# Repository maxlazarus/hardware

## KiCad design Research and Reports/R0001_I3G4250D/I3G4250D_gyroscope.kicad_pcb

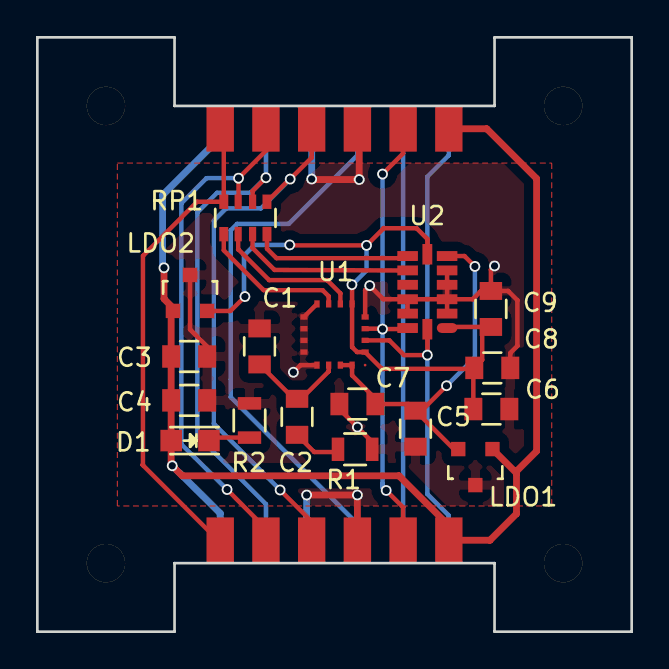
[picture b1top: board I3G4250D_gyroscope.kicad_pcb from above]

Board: 2 copper layers, 33.0 x 33.0 mm, 19 parts (0 on the bottom side), 19 nets.

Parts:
C1: 10nF; C_0805
C2: 0.47uF; C_0805
C3, C4, C5, C6: 1uF; C_0805
C7: 10uF tantalum; C_0805
C8, C9: 0.1uF; C_0805
D1: POW; LED-0805
J1: modular8_rev3_comms_in; modular8_rev3_edge
J2: modular8_rev3_comms_out; modular8_rev3_edge
LDO1, LDO2: AP7313-33SAG-7; SOT-23
R1: 10k; R_0805
R2: 680; R_0805
RP1: R_PACK4; R_Array_Convex_4x0603
U1: I3G4250DTR; LGA-16
U2: ADXL343; LGACC-14-1

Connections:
+3.3VP: C5.1, C7.1, LDO1.2, U1.15, U1.16, U2.6
+3V3: C6.1, C8.1, C9.1, LDO2.2, U1.1, U1.5, U2.1, U2.7
+5V: C3.1, C4.1, D1.2, J1.2, J1.11, J2.1, J2.12, LDO1.1, LDO2.1
/SCL: J1.12, J2.2, U1.2, U2.14
/SDA: J1.9, J2.3, U1.3, U2.13
/THRU1: J1.1, J2.11, RP1.4
/THRU2: J1.3, J2.9, RP1.3
/THRU3: J1.5, J2.7, RP1.1
/THRU4: J1.10, J2.4
/THRU5: J1.8, J2.6
/THRU6: J1.4, J2.10, RP1.2
/U1_INT1: RP1.5, U1.7
/U1_INT2: RP1.6, U1.6
/U2_INT1: RP1.8, U2.8
/U2_INT2: RP1.7, U2.9
GND: C1.2, C3.2, C4.2, C5.2, C6.2, C7.2, C8.2, C9.2, J1.6, J1.7, J2.5, J2.8, LDO1.3, LDO2.3, R1.2, R2.2, U1.4, U1.8, U1.9, U1.10, U1.11, U1.12, U1.13, U2.2, U2.3, U2.4, U2.5, U2.11, U2.12
unnamed: C1.1, C2.1, U1.14
unnamed: C2.2, R1.1
unnamed: D1.1, R2.1

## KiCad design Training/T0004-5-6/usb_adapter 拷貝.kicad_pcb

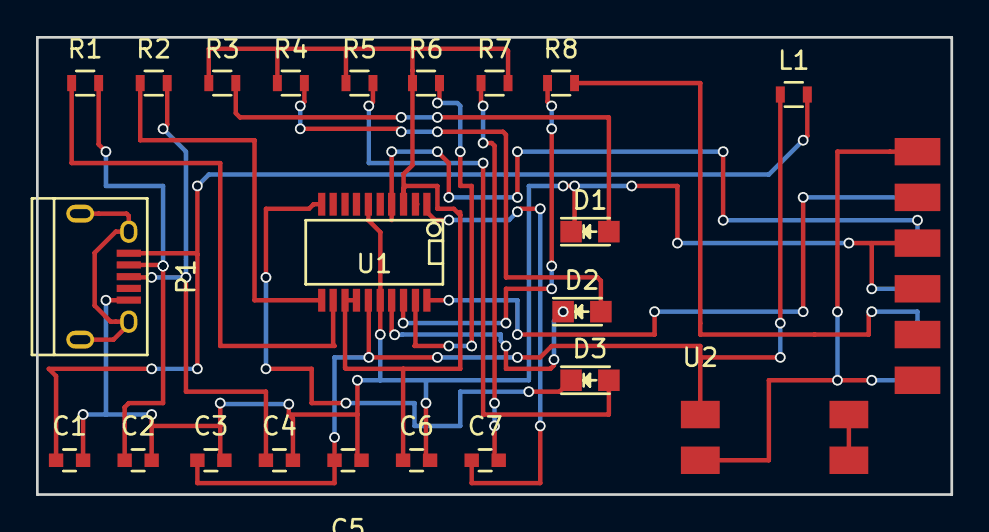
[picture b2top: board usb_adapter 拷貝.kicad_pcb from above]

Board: 2 copper layers, 50.8 x 25.4 mm, 23 parts (0 on the bottom side), 21 nets.

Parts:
C1: 10nF; C_0603
C2, C4: 47pF; C_0603
C3: 4.7uF; C_0603
C5, C6, C7: 0.1uF; C_0603
D1: POW; LED-0805
D2: RX; LED-0805
D3: TX; LED-0805
J1: modular8_rev3_comms_out; modular8_rev3_edge
L1: FERRITE BEAD; R_0603
P1: USB_OTG; USB_Micro-B
R1, R2: 27; R_0603
R3, R4, R5: 680; R_0603
R6, R7, R8: 10k; R_0603
U1: FT231X; SSOP-20
U2: TE_1825058-1; DIPSWITCH_SMT_ALCO_2CCT

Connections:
+3V3: C6.1, R3.1, R4.1, R5.1, R6.1, R7.2, U1.3, U1.13, U1.14
+5V: C3.1, C5.1, L1.1, U1.15, U2.1
/POWER_OUT: J1.1, J1.12, U2.2
/PROGRAM: C7.2, R7.1
/RX: J1.6, U1.4
/TX: J1.4, U1.20
/TXDEN: R8.1, U1.18
/~RXLED: D2.1, U1.17
/~SLEEP: R6.2, U1.19
/~TXLED: D3.1, U1.10
GND: C1.2, C2.2, C3.2, C4.2, C5.2, C6.2, D1.1, J1.5, J1.8, P1.5, U1.6, U1.16
unnamed: C1.1, L1.2, P1.1
unnamed: C2.1, P1.2, R1.2
unnamed: C4.1, P1.3, R2.2
unnamed: C7.1, U1.1
unnamed: D1.2, R3.2
unnamed: D2.2, R4.2
unnamed: D3.2, R5.2
unnamed: J1.10, R8.2
unnamed: R1.1, U1.12
unnamed: R2.1, U1.11
